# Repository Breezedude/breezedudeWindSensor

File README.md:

# Breezedude Wind Station
### An open source, solar powered FANET wind station for paragliding and hang gliding sites

The Breezedude measures wind speed, gusts, wind direction, temperature and air
pressure at your launch or landing site and sends them over FANET, a free radio
network. FANET varios nearby show the data directly, and every ground station in
range passes it on to the internet, where it appears on the
[Breezedude map](https://breezedude.de/) and on the OGN. No SIM card, no
subscription: a small solar panel and a battery keep it running.

<p align="center">
  
  <br>
  
</p>

## Where to start

**[install.breezedude.de](https://install.breezedude.de/) is the place for
everything you need to set up and run a station** (in German). You do not need
anything from this repository for that.

| You want to | Go to |
|---|---|
| Find out whether a ground station covers your site | [Ground station map](https://gsmap.breezedude.de) and the [FAQ](https://install.breezedude.de/faq.html) |
| Buy a complete set or the parts | [Where to buy](https://install.breezedude.de/where-to-buy.html) |
| Assemble and mount the station | [Setup guide](https://install.breezedude.de/setting-up-a-breezedude.html) |
| Set the name, position and sensor | [Configurator](https://install.breezedude.de/configurator.html): it writes the `settings.txt` for you |
| See what the station is doing, find faults | [USB diagnosis](https://install.breezedude.de/tools/breezedude-analyze.html) in Chrome or Edge |
| Update the firmware | [Software update](https://install.breezedude.de/tools/breezedude-update.html) |
| Build a ground station of your own | [Ground station](https://install.breezedude.de/groundstation.html) and [BreezedudeGS](https://github.com/Breezedude/breezedudeGS) |
| Read about hardware versions, repeaters and compatibility | [Wind station](https://install.breezedude.de/windstation.html) |
| Manage your stations, configure and update them over the air | [Device management](https://devices.breezedude.de/) |

## Questions, problems, ideas

**Ask in the [Discussions](https://github.com/Breezedude/breezedudeWindSensor/discussions).**
Other station owners read along there, and many questions have been answered
before, so a quick search often helps. When you ask about a station, the most
useful details are:

- the station ID (for example `BD1234`) and its firmware version, both shown by the
  [USB diagnosis](https://install.breezedude.de/tools/breezedude-analyze.html)
- the wind sensor you use
- what the LEDs do: blue blinks when the station sends, red means it found a problem
- the log from the USB diagnosis, if the station does not behave as expected

## How it works

1. The wind sensor on the mast measures, the Breezedude transmitter in the box
   below it reads the sensor and averages the values.
2. Every 40 seconds the station sends wind, gusts, direction, temperature and
   pressure over FANET on 868 MHz.
3. FANET varios in the air receive the packets directly. A ground station in range
   forwards them to the OGN and to [breezedude.de](https://breezedude.de/).

With a clear line of sight a ground station 30 km away and more is no problem.
Behind trees, buildings or a ridge the range can drop to a few kilometres. For a
station hidden behind a mountain, a second Breezedude on the summit can work as a
**repeater** and pass its packets on. The
[wind station page](https://install.breezedude.de/windstation.html#reichweite)
explains the repeater modes; the scheduled repeater only switches its receiver on
when a packet is due and gets by on very little power.

## What is in the box

- **Transmitter board** with a SAMD21 microcontroller, USB-C, SMA antenna connector
  and charging for a 1S Li-Ion battery (16340) from a 5 V solar panel
- **LoRa module LLCC68** for FANET on 868 MHz
- **Barometer HP203B** for pressure and temperature

Supported wind sensors:

- **Ecowitt WS85** in UART mode: recommended, best supported, part of the complete set
- **Davis 6410**: analog anemometer with reed contact and potentiometer
- **Ecowitt WS80**: works, but needs more adaptation

Power use averaged over the 40 s send interval, measured on the bench at the
battery: about 0.3 mA with a Davis 6410 and about 0.8 mA with a WS85.

## Firmware updates

Stations within reach of a Breezedude ground station can be updated over the air,
and their settings can be changed remotely in the
[device management](https://devices.breezedude.de/). Otherwise connect the station
by USB and follow the [update guide](https://install.breezedude.de/tools/breezedude-update.html).
Firmware releases are published on the
[releases page](https://github.com/Breezedude/breezedudeWindSensor/releases).

## For developers

- Firmware: PlatformIO, Adafruit SAMD core and the ItsyBitsy M0 variant definitions.
  `pio run` builds `build/ota/breezedude-ota-<version>.bin` and a UF2 image.
- Host tests for the logic that runs without hardware: `testing/host/run_all.bat`
  (needs Visual Studio's `cl.exe`).
- The HWInfo radio report is described in [doc/hwinfo-protocol.md](doc/hwinfo-protocol.md).
- Hardware: [breezedudeWindSensor-pcb](https://github.com/Breezedude/breezedudeWindSensor-pcb)
- Bootloader: [bootloader_samd21_breezedude](https://github.com/Breezedude/bootloader_samd21_breezedude)
- [Wiki](https://github.com/Breezedude/breezedudeWindSensor/wiki)

#### Related projects and inspiration
* https://github.com/gereic/GXAirCom
* https://github.com/jgromes/RadioLib
* https://github.com/3s1d/fanet-stm32
* https://github.com/adafruit/ArduinoCore-samd and https://github.com/adafruit/uf2-samdx1

## License

Hardware and software are licensed for non-commercial use only, see [LICENSE.txt](LICENSE.txt).

If you like this project

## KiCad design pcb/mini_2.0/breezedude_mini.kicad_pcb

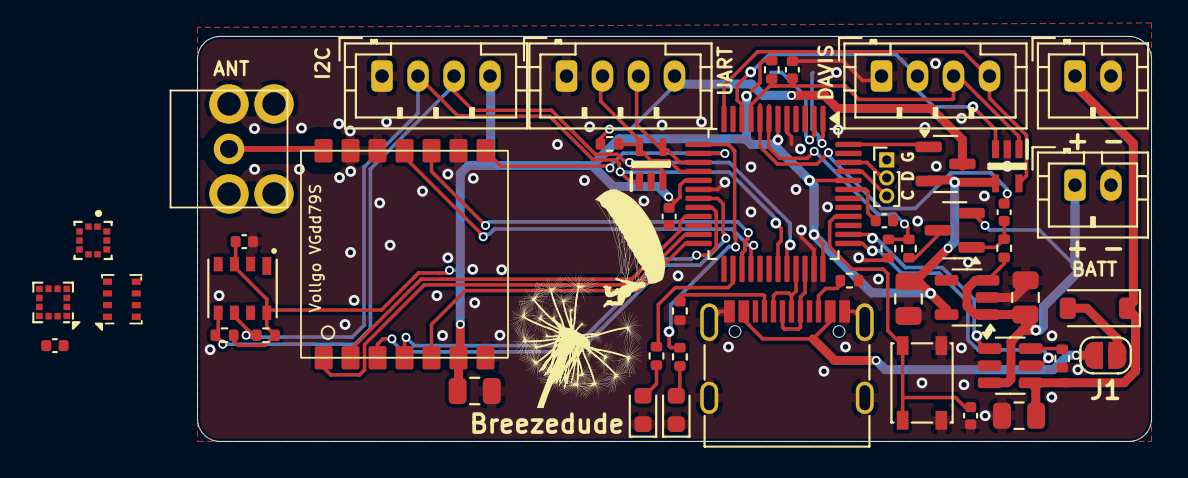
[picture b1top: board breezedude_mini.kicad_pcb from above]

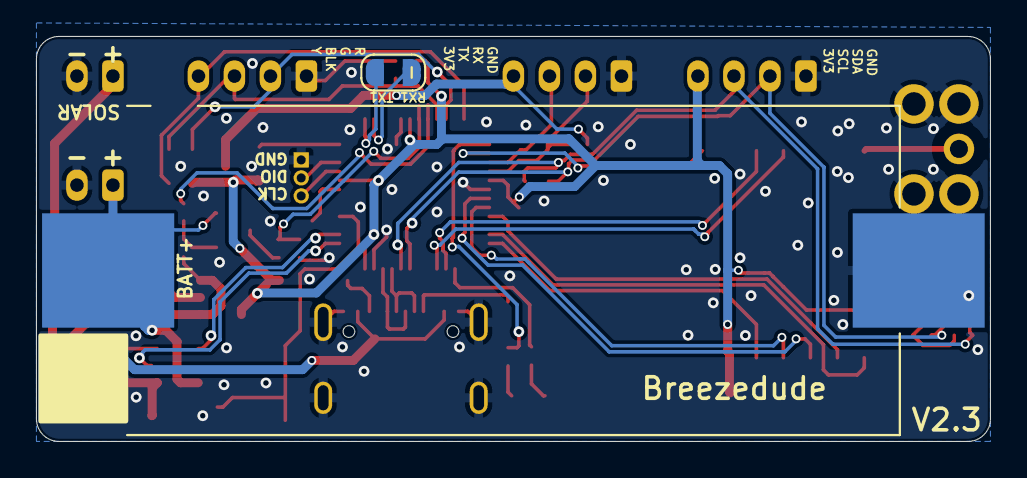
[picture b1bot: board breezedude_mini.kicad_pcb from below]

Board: 2 copper layers, 53.0 x 22.5 mm, 50 parts (2 on the bottom side), 46 nets.

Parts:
AE1: Antenna_Shield; sma_edge_6.5mm_vert
BT1: 1050; BAT_1050
C1, C3, C4, C12: 47u 6.3V; C_0805_2012Metric
C2, C6, C8: 10u 6.3V; C_0402_1005Metric
C5, C9, C11: 100n 16V; C_0402_1005Metric
C10: 220n 16V; C_0402_1005Metric
D1, D2: SMF3.3.TCT; SOT65P210X110-5N
D3: LED blue; LED_0603_1608Metric
D4: LED red; LED_0603_1608Metric
D5: Diode; D_SOD-123
J1, J6: Conn_01x02_Pin; JST_PH_B2B-PH-K_1x02_P2.00mm_Vertical
J2, J3, J5: Conn_01x04_Pin; JST_PH_B4B-PH-K_1x04_P2.00mm_Vertical
J4: Conn_01x03_Pin; PinHeader_1x03_P1.00mm_Vertical
J7: USB_C_Receptacle_USB2.0_16P; USB_C_Receptacle_G-Switch_GT-USB-7010ASV
J8: Conn_01x02_Pin; SolderJumper-2_Open_Gap1mm
JP1: SolderJumper_2_Open; SolderJumper-2_P1.3mm_Open_RoundedPad1.0x1.5mm
Q1, Q2: P-MOS; SOT-23
R1, R3, R12: 10k; R_0402_1005Metric
R2, R5: 100k; R_0402_1005Metric
R4: 330k; R_0402_1005Metric
R6: 470; R_0402_1005Metric
R7: 200; R_0402_1005Metric
R8, R9: 3.3k; R_0402_1005Metric
R10, R11: 5.1k; R_0402_1005Metric
SW1: SW_Push; SW_SPST_PTS810
U2: STLQ015M33R; SOT-23-5
U3: ATSAMD21G18A-A; TQFP-48_7x7mm_P0.5mm
U4: LIS2MDL; LGA-12_2x2mm_P0.5mm
U5: BMP280; Bosch_LGA-8_2x2.5mm_P0.65mm_ClockwisePinNumbering
U6: vollgo_vgdd79s868n0s1
U7: BMP388; PQFN50P200X200X80-10N
U8: HP203B; HP203B-LGA8
U9: TP4057; TSOT-23-6

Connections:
3V3: C4.2, C6.2, C8.2, C12.2, D1.4 (I/O4), J2.4, Q1.2 (S), R2.1, R8.2, R9.2, U2.5 (VOUT), U3.6 (VDDANA), U3.17 (VDDIO), U3.36 (VDDIO), U3.44 (VDDIN), U4.9 (Vdd), U4.10 (Vdd_IO), U5.2 (CSB), U5.6 (VDDIO), U5.8 (VDD), U6.6 (VCC), U7.1 (VDDIO), U7.6 (CSB), U7.10 (VDD), U8.3 (VDD), U8.8 (CSB)
/ANT: AE1.1 (A), U6.14 (ANT)
/BATT+: BT1.P, C3.2, J1.1, Q2.2 (S), R3.1, U2.1 (VIN), U2.3 (EN), U9.3 (BAT)
/DAVIS_DIR: D1.3 (I/O3), J3.2, U3.10 (PA05)
/DAVIS_POWER: D1.5 (I/O2), J3.4, U3.12 (PA07)
/DAVIS_SPEED: C5.1, D1.1 (I/O1), J3.3, R2.2, U3.9 (PA04)
/LED1: R6.1, U3.26 (PA17)
/LED2: R7.1, U3.13 (PA08)
/LORA_CS: U3.24 (PA15), U6.5 (CS)
/LORA_DIO1: U3.27 (PA18), U6.10 (DIO1)
/LORA_DIO2: U3.28 (PA19), U6.11 (BUSY)
/LORA_DIO3: U3.14 (PA09), U6.8 (DIO3)
/LORA_MISO: U3.21 (PA12), U6.2 (MISO)
/LORA_MOSI: U3.19 (PB10), U6.3 (MOSI)
/LORA_RESET: U3.23 (PA14), U6.1 (RST)
/LORA_SCK: U3.20 (PB11), U6.4 (SCK)
/PV_CHARGE: U3.38 (PB23), U9.1 (~CHRG)
/PV_DONE: U3.37 (PB22), U9.5 (STDBY)
/RESET: C11.2, SW1.1, U3.40 (~RESET)
/RX: D2.5 (I/O2), J5.2, R12.1, U3.16 (PA11)
/RX1: J8.2, U3.2 (PA01)
/SCL: D2.3 (I/O3), J2.3, R8.1, U3.32 (PA23), U4.1 (SCL/SPC), U5.4 (SCK), U7.2 (SCK), U8.5 (SCL)
/SDA: D2.1 (I/O1), J2.2, R9.1, U3.31 (PA22), U4.4 (SDA/SDI/SDO), U5.3 (SDI), U7.4 (SDI), U8.6 (SDA)
/SOLAR+: C1.2, D5.1 (K), J6.1, U9.4 (V_{CC})
/SWDCLK: J4.3, U3.45 (PA30)
/SWDIO: J4.2, U3.46 (PA31)
/TX: D2.4 (I/O4), J5.3, U3.15 (PA10)
/TX1: J8.1, U3.1 (PA00)
/USB_N: J7.A7 (D-), J7.B7 (D-), U3.33 (PA24)
/USB_P: J7.A6 (D+), J7.B6 (D+), U3.34 (PA25)
/V_DIV: R4.2, R5.1, U3.7 (PB08)
/V_IMP: C9.2, U3.8 (PB09)
GND: AE1.2 (Shield), BT1.N, C1.1, C2.1, C3.1, C4.1, C5.2, C6.1, C8.1, C10.2, C11.1, C12.1, D1.2 (GND), D2.2 (GND), D3.1 (K), D4.1 (K), J1.2, J2.1, J3.1, J4.1, J5.1, J6.2, J7.A1 (GND), J7.A12 (GND), J7.B1 (GND), J7.B12 (GND), J7.S1 (SHIELD), R1.2, R5.2, R10.2, R11.2, SW1.2, U2.2 (GND), U3.5 (GNDANA), U3.18 (GND), U3.35 (GND), U3.42 (GND), U4.6 (GND), U4.8 (GND), U5.1 (GND), U5.7 (GND), U6.7 (GND), U6.9 (GND), U6.12 (GND), U6.13 (GND), U7.3 (VSS), U7.5 (SDO), U7.8 (VSS), U7.9 (VSS), U8.2 (GND), U9.2 (GND)
unnamed: D3.2 (A), R6.2
unnamed: D4.2 (A), R7.2
unnamed: D5.2 (A), JP1.2 (B)
unnamed: J7.A5 (CC1), R10.1
unnamed: J7.B5 (CC2), R11.1
unnamed: J7.A4 (VBUS), J7.A9 (VBUS), J7.B4 (VBUS), J7.B9 (VBUS), JP1.1 (A)
unnamed: Q2.3 (D), R4.1
unnamed: C9.1, Q2.1 (G), R3.2
unnamed: C2.2, U3.43 (VDDCORE)
unnamed: C10.1, U4.5 (C1)
unnamed: R1.1, U9.6 (PROG)
SW_WS: Q1.1 (G), U3.48 (PB03)
VCC_WS: J5.4, Q1.3 (D), R12.2

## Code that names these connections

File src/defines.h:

#pragma once

#define BROADCAST_INTERVAL 40*1000UL // dafault value,  overwritten by settingfile

#define LORA_FREQ_EU 868.2
#define LORA_BW_EU 250
#define LORA_FREQ_NA 920.8
#define LORA_BW_NA 500

#define DEBUGSER Serial2
#define SENSOR_UART Serial1
#define GPS_SERIAL Serial1 // if no WS80 is connected a GPS receiver can be used. Mainly for OGN range/coverage check

// https://github.com/adafruit/ArduinoCore-samd/blob/master/variants/itsybitsy_m0/variant.cpp
// 0 { PORTA, 11, PIO_SERCOM, (PIN_ATTR_DIGITAL), No_ADC_Channel, NOT_ON_PWM, NOT_ON_TIMER, EXTERNAL_INT_11 }, // RX: SERCOM0/PAD[3]
// 1 { PORTA, 10, PIO_SERCOM, (PIN_ATTR_DIGITAL), No_ADC_Channel, NOT_ON_PWM, NOT_ON_TIMER, EXTERNAL_INT_10 }, // TX: SERCOM0/PAD[2]

// SERCOM 4 - SPI RFM95W LoRa
#define PIN_LORA_MISO MISO  // 28 PA12  - SERCOM2/PAD[0] | alt SERCOM4/PAD[0]
#define PIN_LORA_MOSI MOSI  // 29 PB10  -                | alt SERCOM4/PAD[2]
#define PIN_LORA_SCK SCK    // 30 PB11  -                | alt SERCOM4/PAD[3]

#define PIN_LORA_CS 5    // PA15 - SERCOM2/PAD[3] | alt SERCOM4/PAD[3]
#define PIN_LORA_RESET 2 // PA14 - SERCOM2/PAD[2] | alt SERCOM4/PAD[2]
#define PIN_LORA_DIO0 11 // PA16 - SERCOM1/PAD[0] | alt SERCOM3/PAD[0]
#define PIN_LORA_DIO1 10 // PA18 - SERCOM1/PAD[2] | alt SERCOM3/PAD[2]
#define PIN_LORA_DIO2 12 // PA19 - SERCOM1/PAD[3] | alt SERCOM3/PAD[3]
#define PIN_LORA_DIO3 3  // PA09 - SERCOM0/PAD[1], ADC
#define PIN_PV_CHARGE 38// PB23
#define PIN_PV_DONE 37 // PB22
#define PIN_PS_WS 36 // PB03 PIO_SERCOM_ALT, PIN_ATTR_NONE, No_ADC_Channel, NOT_ON_PWM, NOT_ON_TIMER, EXTERNAL_INT_NONE },  // SPI Flash MISO on ItsyBitsy M0, Power switch control for WSXX Sensor. HW >= 2.2

// Serial2
#define PIN_SERCOM1_TX 40 // PA00 SERCOM1 PAD0
#define PIN_SERCOM1_RX 41 // PA01 SERCOM1 PAD1

// Pins with solder jumpers 
#define PIN_ID0 6 // PA20 - SERCOM5/PAD[2]
#define PIN_ID1 7 // PA21 - SERCOM5/PAD[3]


#define FANET_VENDOR_ID 0xBD
#define VBATT_LOW 3.35 // Volt


#define PIN_DAVIS_SPEED 17 // A3 17 PA04
#define PIN_DAVIS_DIR 18 // A4 18 PA05
#define PIN_DAVIS_POWER 9 // 9 PA07 - power for direction potentiometer. Turn off if not used to save power. Old Pin, Hardware 2.4 uses PS_SENSOR

// SERCOM 3 - I²C Barometer / Digipot
#define PIN_SDA 26 // PA22
#define PIN_SCL 27 // PA23

// DAVIS6410 Pinout
// Black - Wind speed contact (closure to ground)
// Red - Ground
// Green - Wind direction pot wiper (20KΩ potentiometer)
// Yellow - Pot supply voltage

// SERCOM 0 - uart serial Sensor/ GPS / Debug
#define PIN_RX 0 // A6 PA11
#define PIN_TX 1 // A7 PA10

#define PIN_STATUSLED 13 // PA17 // blue, 1.2mA @ 2.77V = 470Ohm
// Two pins moved with hardware 2.5. The firmware tells the revisions apart at
// boot (hw.cpp) and picks the pin at run time through hw_pin_led_error() and
// hw_pin_v_read(); the old pads are free on 2.5.
#define PIN_ERRORLED_HW24 4   // D4/A8 PA08 - red 2.9mA @ 2.16V = 390Ohm, up to hardware 2.4
#define PIN_ERRORLED_HW25 11  // D11 PA16 - red LED from hardware 2.5 on. The SX1276 build
                              // uses this pin as DIO0; no 2.x board carries that radio.
#define PIN_V_READ_TRIGGER A2 // D16 PB09
#define PIN_V_READ_HW24 A1    // D15 PB08 ADC/AIN[2] - battery divider up to hardware 2.4
#define PIN_V_READ_HW25 A5    // D19 PB02 ADC/AIN[10] - battery divider from hardware 2.5 on
// Hardware identification, from 2.5 on: read against the internal pull-up at
// boot, a revision pulls its pin to ground through 4.7k, boards before 2.5
// leave both open. Both are the unpopulated SPI flash pads of the ItsyBitsy M0.
#define PIN_HW_ID0 39 // PA27 - 4.7k to ground on 2.5
#define PIN_HW_ID1 32 // PA28 - open so far, reserved for the next revision

#define VERSIONFILE (char*) "version.txt"
#define SETTINGSFILE (char*) "settings.txt"



#define WIND_AGE 1000*30 // 30s history
#define GUST_AGE 1000*60*10 // 10 min history
#define WIND_HIST_STEP 1000*4 //ms history slots, 22 sek
#define WIND_HIST_LEN 150 // number so slots. should match GUST_AGE / GUST_HIST_STEP


enum ResParseChar {
  RESP_OK,
  RESP_ERROR,
  RESP_COMPLETE
};

enum LORA_MODULE{
  LORA_NONE,
  LORA_SX1276,
  LORA_SX1262,
  LORA_LLCC68
};

enum CHIP_BARO{
  BARO_NONE,
  BARO_BMP280,
  BARO_SPL06,
  BARO_BMP3xx,
  BARO_HP203B
};

enum CHIP_IMU{
  IMU_NONE,
  IMU_
};


enum Wakeup_Source{
  WAKEUP_NONE,
  WAKEUP_RTC,
  WAKEUP_EIC,
  WAKEUP_WDT,
  WAKEUP_UART,
  // The debug console on SERCOM1, kept separate from the sensor UART above:
  // a console command has to end the sleep window, a sensor byte must not.
  WAKEUP_CONSOLE,
  WAKEUP_LORA,
  WAKEUP_USB
};

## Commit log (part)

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2025-09-13 V0.6: refactoring, added ws85 uart, small improvements
2025-09-24 V2.3: * Added 10k pullup to Ssensor UART RX to aboid wakeup when no sensor is connected/cable failiure * Replaced CN3063 with TP4057 for better avaliability. * Moved SWD connector for better acessibi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
2025-10-09 add USB serial forwarding of WS85 UART data
2026-03-04 Enhance README with additional resources
    Updated README to include link to Discussions.
2026-03-17 0.7 alpha, restructure, fix macOS filesystem
2026-03-21 efficency improvements
2026-03-24 add usb debugging mode. improve usb logging
2026-03-30 fixed filesystem not writable by samd21
2026-03-31 fix baro values not being set. Add LBT mode, add analog sensor test mode. Frame for hw_info message, wip.
2026-04-08 add HW info messages (beta), possibly fix WS85 unavailability issues due to powering down cause of bad voltage readings
2026-04-08 pre release 0.7.2, see last commit
2026-04-10 add smart rx & forwarding. skip weather sending if no valid data
2026-04-11 Revise README with new project details and formatting
2026-04-14 flash size optimisation. wip
2026-05-02 v1.0.0 beta. OTA Updates, new bootloader.
2026-05-02 fix 7mA during deepsleep issue
2026-05-04 fix ota not finishing
2026-05-07 V1.0.2 cleanup & cosmetics
2026-05-21 add repeater mode
2026-05-26 fix WS80 reading stops
2026-06-05 Add PCB files repository link to README
    Updated README to include new PCB files repository link.
2026-06-11 possibly fix wrong baro values if no humidity sensor present
2026-06-14 ota fix
2026-06-14 flash layout change for V1.1 compatible with bootloader V4.2
